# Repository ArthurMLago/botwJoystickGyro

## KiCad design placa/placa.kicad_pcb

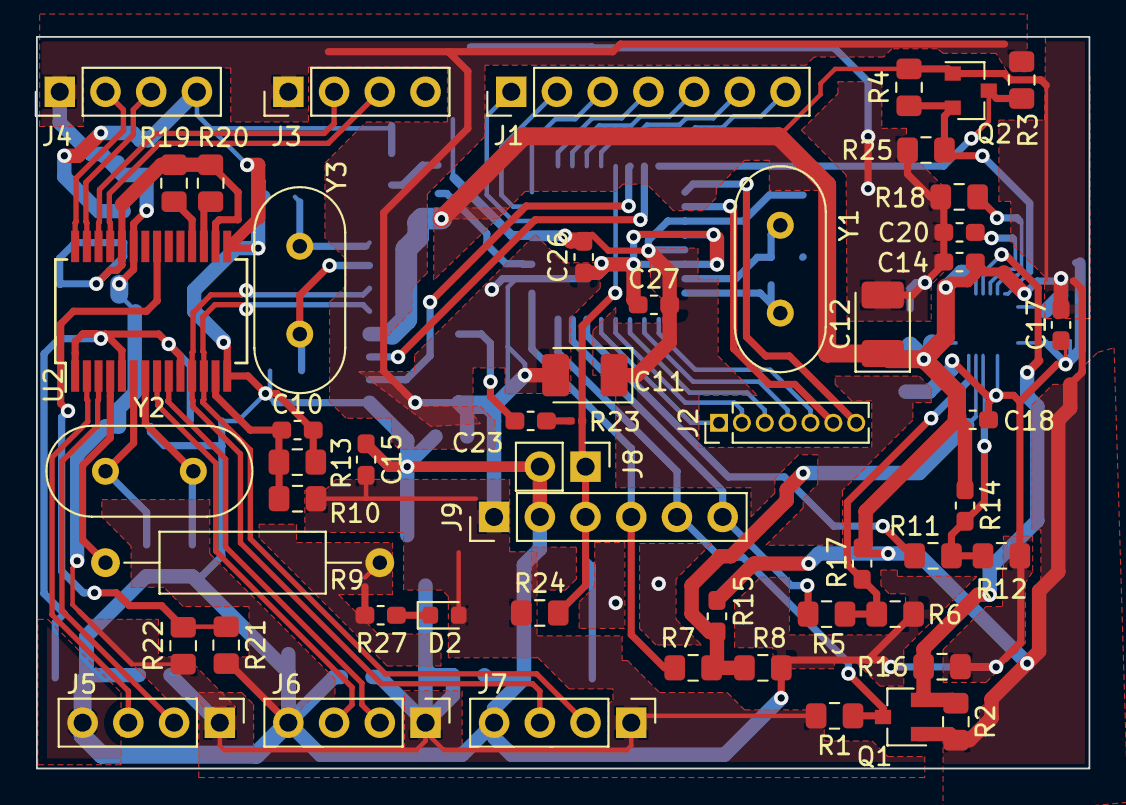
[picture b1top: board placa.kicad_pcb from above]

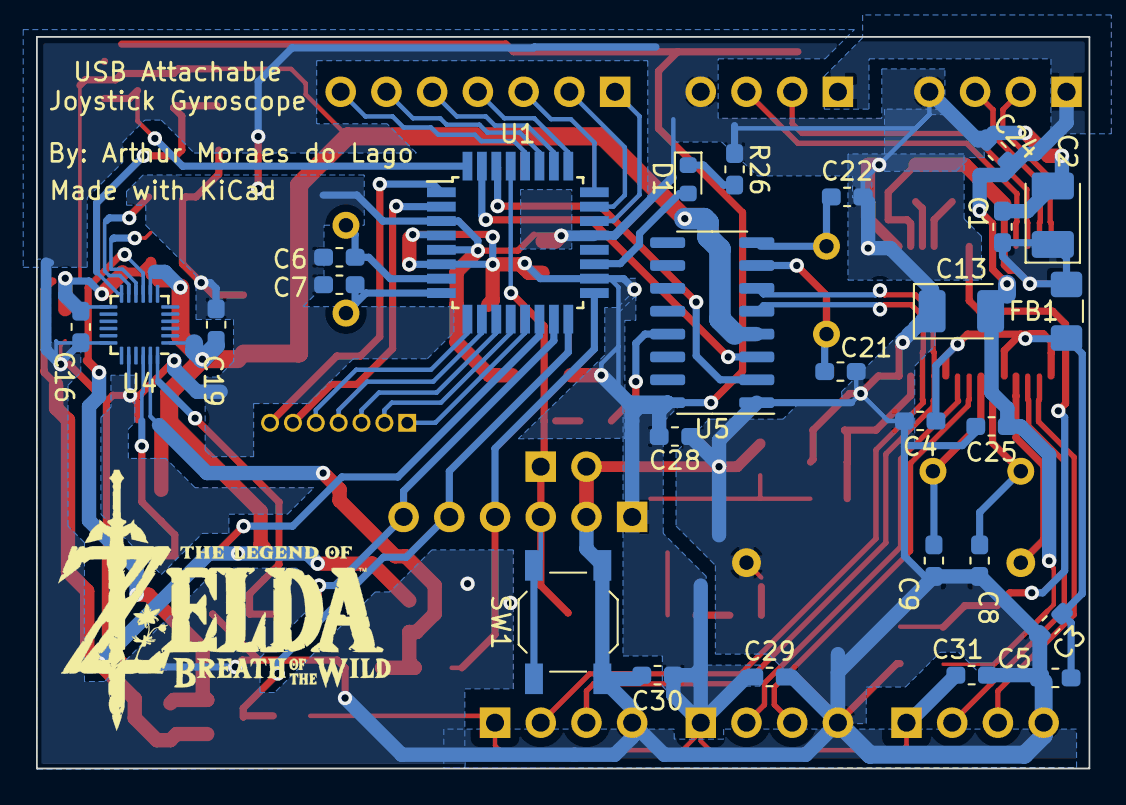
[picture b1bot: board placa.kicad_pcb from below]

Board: 2 copper layers, 58.5 x 40.6 mm, 80 parts (27 on the bottom side), 60 nets.

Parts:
C1, C3, C4, C5, C23, C24, C25, C26, C27, C28, C29, C30, C31: 100n; C_0603_1608Metric_Pad1.05x0.95mm_HandSolder
C2: 10u; CP_EIA-3528-12_Kemet-T_Pad1.50x2.35mm_HandSolder
C6, C7, C8, C9, C21, C22: 33pF; C_0603_1608Metric_Pad1.05x0.95mm_HandSolder
C10: 1u; C_0603_1608Metric_Pad1.05x0.95mm_HandSolder
C11, C12, C13: 10uF; CP_EIA-3528-12_Kemet-T_Pad1.50x2.35mm_HandSolder
C14, C15, C16, C17: 100nF; C_0603_1608Metric_Pad1.05x0.95mm_HandSolder
C18: 0.01u; C_0603_1608Metric_Pad1.05x0.95mm_HandSolder
C19, C20: 0.1u; C_0603_1608Metric_Pad1.05x0.95mm_HandSolder
D1, D2: LED; LED_0603_1608Metric
FB1: 600R/2A; R_1206_3216Metric_Pad1.42x1.75mm_HandSolder
J1: Conn_01x07_Male; PinHeader_1x07_P2.54mm_Vertical
J2: Conn_01x07_Male; PinHeader_1x07_P1.27mm_Vertical
J3, J4, J5, J6, J7: Conn_01x04; PinHeader_1x04_P2.54mm_Vertical
J8: Conn_01x02_Male; PinHeader_1x02_P2.54mm_Vertical
J9: Conn_01x06_Male; PinHeader_1x06_P2.54mm_Vertical
Q1, Q2: BSS138; SOT-23
R1, R3: 4.7K; R_0805_2012Metric_Pad1.15x1.40mm_HandSolder
R2, R4: 4.7k; R_0805_2012Metric_Pad1.15x1.40mm_HandSolder
R5, R7, R11: 6.8k; R_0805_2012Metric_Pad1.15x1.40mm_HandSolder
R6, R8, R12, R16, R18, R20, R25: 10k; R_0805_2012Metric_Pad1.15x1.40mm_HandSolder
R9: 680/1%; R_Axial_DIN0309_L9.0mm_D3.2mm_P15.24mm_Horizontal
R10, R21, R24: 10K; R_0805_2012Metric_Pad1.15x1.40mm_HandSolder
R13: 47K; R_0805_2012Metric_Pad1.15x1.40mm_HandSolder
R14, R15, R17: 100k; R_0603_1608Metric_Pad1.05x0.95mm_HandSolder
R19: 47k; R_0805_2012Metric_Pad1.15x1.40mm_HandSolder
R22: 5.1K; R_0805_2012Metric_Pad1.15x1.40mm_HandSolder
R23: 0; R_0201_0603Metric
R26, R27: 1k; R_0603_1608Metric_Pad1.05x0.95mm_HandSolder
SW1: SW_Push; SW_SPST_TL3342
U1: ATmega328P-AU; TQFP-32_7x7mm_P0.8mm
U2: GL850G; SSOP-28_5.3x10.2mm_P0.65mm
U4: MPU-9250; InvenSense_QFN-24_3x3mm_P0.4mm_HandSolder
U5: CH340G; SOIC-16_3.9x9.9mm_P1.27mm
Y1: 16MHz; Crystal_HC49-4H_Vertical
Y2, Y3: 12MHz; Crystal_HC49-4H_Vertical

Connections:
/3V_MPU: C12.1, C14.1, C16.1, C17.1, C18.1, C19.1, Q1.1, Q2.1, R2.2, R4.2, R14.1, R15.1, R17.1, U4.1, U4.8, U4.13, U5.4
/5V: C11.2, C13.2, C15.2, C24.1, C25.1, C26.1, C27.1, C28.1, C29.1, C30.1, C31.1, D2.2, J3.1, J4.1, J5.1, J6.1, J7.1, J9.1, R1.2, R3.2, R10.2, R22.1, R24.1, U1.4, U1.6, U1.18, U2.23, U5.16
/AVDD: C3.1, C4.1, C5.1, FB1.1, U2.1, U2.5, U2.10
/V33: C1.1, C2.1, FB1.2, R19.1, R20.1, U2.16, U2.24
AD0: J1.2, U1.23
AD1: J1.3, U1.24
AD2: J1.4, U1.25
AD3: J1.5, U1.26
AD4: J1.6, U1.27
AD5: J1.7, U1.28
AD7: J1.1, U1.22
CH_RX: U1.31, U5.3
CH_TX: U1.30, U5.2
D0+: J3.2, U2.26
D0-: J3.3, U2.25
D1+: J4.2, U2.28
D1-: J4.3, U2.27
D2+: J5.2, U2.3
D2-: J5.3, U2.2
D3+: J6.2, U2.9
D3-: J6.3, U2.8
D4+: J7.2, U2.12, U5.5
D4-: J7.3, U2.11, U5.6
GND: C1.2, C2.2, C3.2, C4.2, C5.2, C6.1, C7.1, C8.2, C9.2, C10.2, C11.1, C12.2, C13.1, C14.2, C15.1, C16.2, C17.2, C18.2, C19.2, C20.2, C21.2, C22.2, C24.2, C25.2, C26.2, C27.2, C28.2, C29.2, C30.2, C31.2, J3.4, J4.4, J5.4, J6.4, J7.4, J8.2, J9.2, R6.2, R8.2, R9.2, R12.2, R13.2, R16.2, R18.2, R21.2, R25.2, R26.2, R27.1, SW1.2, U1.3, U1.5, U1.21, U2.14, U2.15, U4.18, U4.20, U5.1
GPIO0: J2.2, U1.12
GPIO1: J2.1, U1.13
GPIO2: J2.7, U1.1
GPIO3: J2.6, U1.2
GPIO4: J2.5, U1.9
GPIO5: J2.4, U1.10
GPIO6: J2.3, U1.11
INT: Q2.2, R4.1, R25.1, U4.12
MISO: Q1.2, R2.1, R16.1, U4.9
MOSI: R5.2, R6.1, R17.2, U4.24
unnamed: C6.2, U1.7, Y1.1
unnamed: C7.2, U1.8, Y1.2
unnamed: C8.1, U2.6, Y2.1
unnamed: C9.1, U2.7, Y2.2
unnamed: C10.1, R10.1, R13.1, U2.13
unnamed: C20.1, U4.10
unnamed: C21.1, U5.7, Y3.1
unnamed: C22.1, U5.8, Y3.2
unnamed: C23.1, R23.2
unnamed: C23.2, U5.13
unnamed: D1.1, R26.1
unnamed: D1.2, U1.19
unnamed: D2.1, R27.2
unnamed: J9.4, R7.1, U1.17
unnamed: J9.5, Q1.3, R1.1, U1.16
unnamed: J9.6, R5.1, U1.15
unnamed: Q2.3, R3.1, U1.32
unnamed: R9.1, U2.4
unnamed: R11.1, U1.14
unnamed: R18.1, U4.11
unnamed: R19.2, U2.18
unnamed: R20.2, U2.17
unnamed: R21.1, R22.2, U2.21
RESET: J8.1, J9.3, R23.1, R24.2, SW1.1, U1.29
SCLK: R7.2, R8.1, R15.2, U4.23
nCS: R11.2, R12.1, R14.2, U4.22
